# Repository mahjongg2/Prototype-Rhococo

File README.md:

# Prototype-Rhococo
Prototype of my Retro Home color computer, a 8-bit Z80 based home computer remake with 128 (bank switched) RAM, that uses a Parallax propeller chip for all the stuff that homecomputers from the previous century did with lots of simple CMOS logic circuits and sometimes dedicated VLSI chips did, such as generating TV pictures, and sound.
My rhococo should be able to generate 27 colors of VGA video in 512 x 480 resolution, and should be able to generate PSG quality sound. 
instead of relying on cassette tapes, of floppy-disks, it can use SD-cards. It doesn't store its permanent memory on (E)PROMS but on a serial EEPROM read out by the propeller,and copied to Z80 RAM at boot time. 
Its not based on any one retro computer but borrows ideas from all of them, mainly from the sinclair spectrum, Commodore 64, and MSX computers.

on these page I will commit CAD files, (main page is Rhococo.sch with sub-schematics Z80CPU+RAM.sch, and KEYBOARD.sch, and RHOCOCO.kicad.PCB for the layout) , but eventually I will also upload ideas, code and other stuff so that others can also build and test prototypes of my retro home computer.

Note that I explicitly call this a prototype, as Rhococo is still in development, and not a fully functioning device.
Lots of things are not even tested yet, as for testing them other stuff must work first.

If hardware bugs are found I will upload updated files fo new PCBś, and/or information to patch existing PCB's.

Weekly updated information and progress reports will be posted on my Wiki at: https://revspace.nl/Designing_the_RhoCoCo_Retro_Home_COlor_COmputer_hardware

if you want to discuss this meaterial with me, the best place for now would be here: https://www.raspberrypi.org/forums/viewtopic.php?f=62&t=226889

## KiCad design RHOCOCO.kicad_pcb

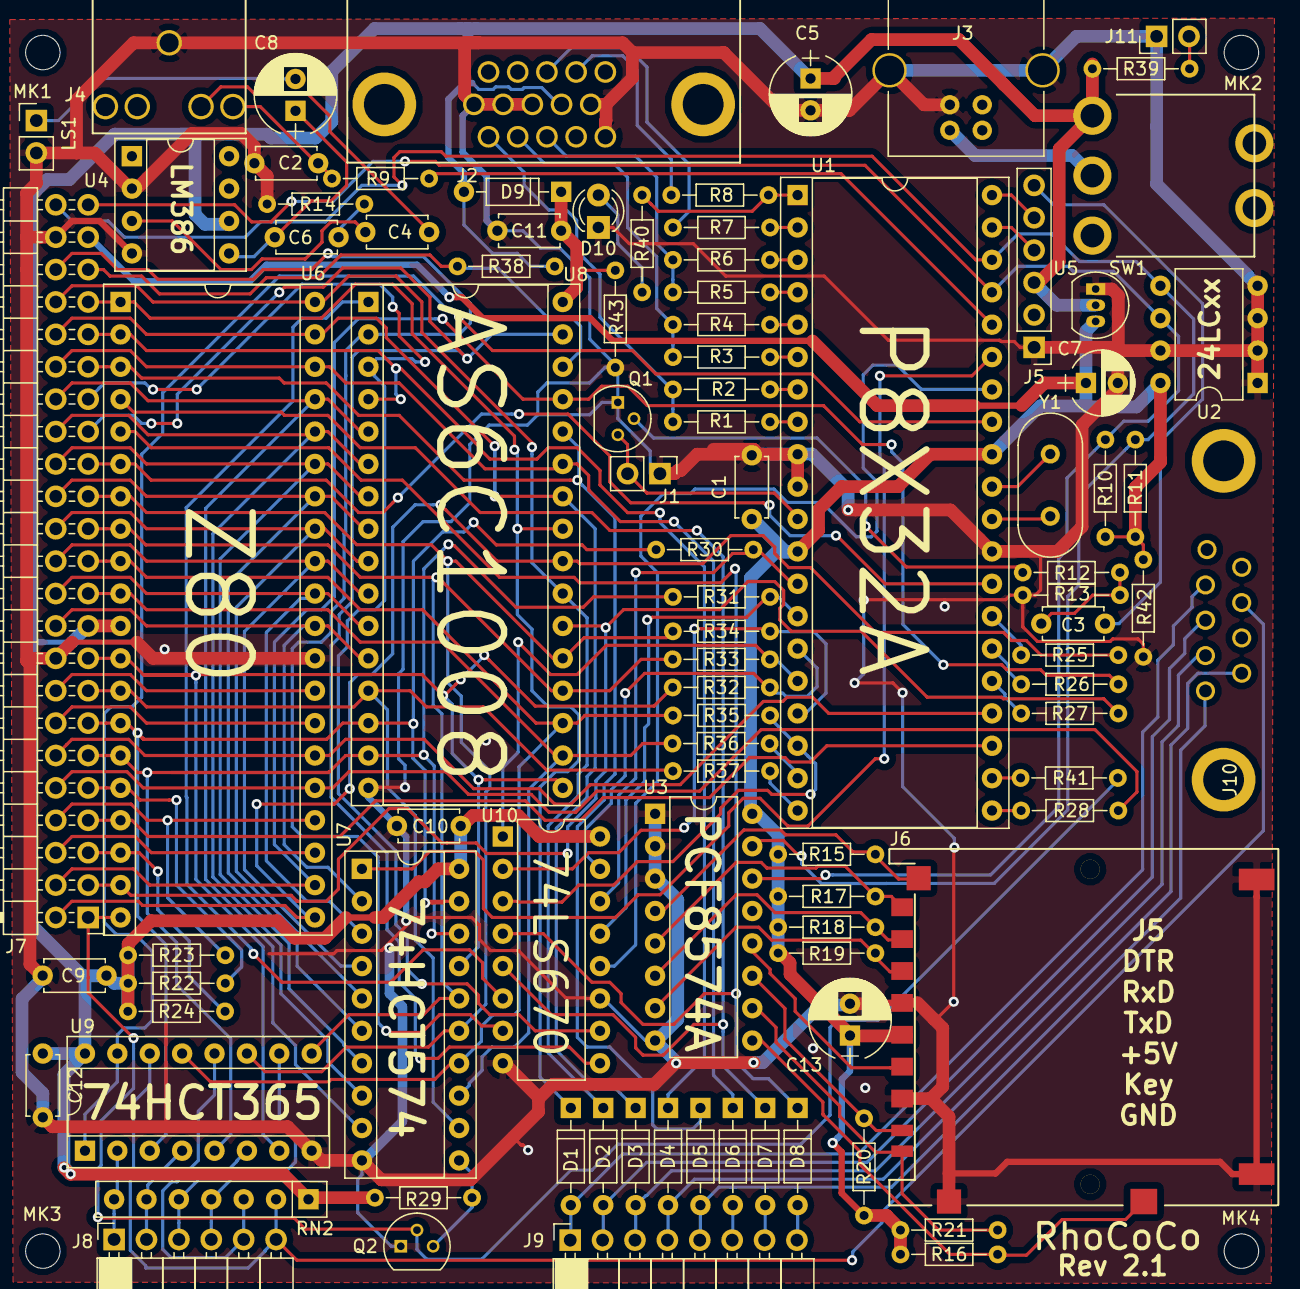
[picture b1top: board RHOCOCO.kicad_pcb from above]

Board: 2 copper layers, 97 parts (0 on the bottom side), 119 nets.

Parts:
C1, C3, C4, C9, C10, C11, C12: 100nF; C_Disc_D4.7mm_W2.5mm_P5.00mm
C2: 10nF; C_Disc_D4.7mm_W2.5mm_P5.00mm
C5: 100uF 16V; CP_Radial_D6.3mm_P2.50mm
C6: 4.7nF; C_Disc_D4.7mm_W2.5mm_P5.00mm
C7: 10uF 16V; CP_Radial_D5.0mm_P2.50mm
C8, C13: 220uF 10V; CP_Radial_D6.3mm_P2.50mm
D1, D2, D3, D4, D5, D6, D7, D8, D9: 1N4148; D_DO-35_SOD27_P7.62mm_Horizontal
D10: LED; LED_D3.0mm
J1, J11: CONN_01X02; Pin_Header_Straight_1x02_Pitch2.54mm
J2: VGA; VGA_connector
J3: USB_B
J4: Audio-Jack-3_2Switches; SPC21348
J5: CONN_01X06; Pin_Header_Straight_1x06_Pitch2.54mm
J6: SD_Card; SD-67600-006
J7: CONN_02X23; Pin_Header_Angled_2x23_Pitch2.54mm
J8: CONN_01X06; Socket_Strip_Angled_1x06_Pitch2.54mm
J9: CONN_01X08; Socket_Strip_Angled_1x08_Pitch2.54mm
J10: DB9_MALE; dB09-MALE
LS1: Speaker; Pin_Header_Straight_1x02_Pitch2.54mm
MK1, MK2, MK3, MK4: Mounting_Hole; MountingHole_2.7mm_M2.5
Q1: 2N3904; TO-92_Molded_Narrow
Q2: 2N7000; TO-92_Molded_Narrow
R1, R3, R5, R7, R8: 240R; R_Axial_DIN0204_L3.6mm_D1.6mm_P7.62mm_Horizontal
R2, R4, R6: 470R; R_Axial_DIN0204_L3.6mm_D1.6mm_P7.62mm_Horizontal
R9, R13, R15, R16, R22, R23, R24, R25, R26, R27, R28, R29, R38, R41: 10K; R_Axial_DIN0204_L3.6mm_D1.6mm_P7.62mm_Horizontal
R10, R11, R43: 4K7; R_Axial_DIN0204_L3.6mm_D1.6mm_P7.62mm_Horizontal
R12: 270; R_Axial_DIN0204_L3.6mm_D1.6mm_P7.62mm_Horizontal
R14: 10; R_Axial_DIN0204_L3.6mm_D1.6mm_P7.62mm_Horizontal
R17, R18, R19, R20, R21: 100K; R_Axial_DIN0204_L3.6mm_D1.6mm_P7.62mm_Horizontal
R30, R31, R32, R33, R34, R35, R36, R37, R40: 1K; R_Axial_DIN0204_L3.6mm_D1.6mm_P7.62mm_Horizontal
R39: 270R; R_Axial_DIN0204_L3.6mm_D1.6mm_P7.62mm_Horizontal
R42: 3K3; R_Axial_DIN0204_L3.6mm_D1.6mm_P7.62mm_Horizontal
RN2: 4K7 x 6 SIP; R_Array_SIP7
SW1: SW_SPDT; SWITCH-300SP1J1BLKM6QE
U1: P8X32A; DIP-40_W15.24mm_Socket
U2: 24LC256; DIP-8_W7.62mm
U3: PCF8574A; DIP-16_W7.62mm
U4: LM386; DIP-8_W7.62mm_Socket
U5: MCP1700-3302E_TO92; TO-92_Inline_Narrow_Oval
U6: Z80CPU; DIP-40_W15.24mm_Socket
U7: 74HCT574; DIP-20_W7.62mm_Socket
U8: AS6C1008; DIP-32_W15.24mm_Socket
U9: 74HCT365; DIP-16_W7.62mm_Socket
U10: 74HCT670; DIP-16_W7.62mm
Y1: 5MHz; Crystal_HC49-U_Vertical

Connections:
+3V3: C1.1, C7.1, C13.1, J6.4, J7.43, R10.2, R11.2, R15.2, R16.2, R17.2, R18.2, R19.2, R20.2, R21.2, R42.2, U1.12, U1.32, U2.8, U3.16, U5.3
+5V: C5.1, C9.2, C10.1, C12.1, D9.2, J2.9, J5.3, J7.19, R22.2, R23.2, R24.2, R29.1, R38.2, R39.2, RN2.1, SW1.1, U4.6, U5.2, U6.11, U7.20, U9.16, U10.16
/BLUE: J2.3, R5.2, R6.2
/DTR: C3.1, J5.6
/GREEN: J2.2, R3.2, R4.2
/H-SYN: J2.13, R7.2
/PWM_AUDIO: R9.1, U1.36
/RED: J2.1, R1.2, R2.2
/RXD: J5.5, U1.40
/TXD: J5.4, U1.39
/V-SYN: J2.14, R8.2
/z80ram/IORQ: Q2.3, R29.2, U7.11
/z80ram/KEYBOARD/KeyAddress8: D6.2, J9.6
/z80ram/KEYBOARD/KeyAddress9: D3.2, J9.3, J10.2
/z80ram/KEYBOARD/KeyAddress10: D2.2, J9.2, J10.3
/z80ram/KEYBOARD/KeyAddress11: D1.2, J9.1, J10.4
/z80ram/KEYBOARD/KeyAddress12: D4.2, J9.4, J10.6
/z80ram/KEYBOARD/KeyAddress13: D5.2, J9.5, J10.1
/z80ram/KEYBOARD/KeyAddress14: D7.2, J9.7
/z80ram/KEYBOARD/KeyAddress15: D8.2, J9.8
/z80ram/KEYBOARD/KeyData0: J8.1, RN2.7, U9.2
/z80ram/KEYBOARD/KeyData1: J8.2, RN2.6, U9.4
/z80ram/KEYBOARD/KeyData2: J8.3, RN2.5, U9.6
/z80ram/KEYBOARD/KeyData3: J8.4, RN2.4, U9.10
/z80ram/KEYBOARD/KeyData4: J8.5, RN2.3, U9.12
/z80ram/KEYBOARD/KeyData5: J8.6, J10.8, RN2.2, U9.14
/z80ram/RAM-A14: J7.33, U8.3, U10.10
/z80ram/RAM-A15: J7.31, U8.31, U10.9
/z80ram/RAM-A16: J7.42, U8.2, U10.7
/z80ram/RAM-A17: U8.1, U10.6
/z80ram/Z80-A0: J7.20, U6.30, U7.2, U8.12
/z80ram/Z80-A1: J7.22, U6.31, U7.3, U8.11
/z80ram/Z80-A2: J7.24, U6.32, U7.4, U8.10
/z80ram/Z80-A3: J7.26, U6.33, U7.5, U8.9
/z80ram/Z80-A4: J7.28, U6.34, U7.6, U8.8
/z80ram/Z80-A5: J7.30, U6.35, U7.7, U8.7
/z80ram/Z80-A6: J7.32, U6.36, U7.8, U8.6
/z80ram/Z80-A7: J7.34, U6.37, U7.9, U8.5
/z80ram/Z80-D6: J7.21, R36.1, U6.10, U7.13, U8.18
/z80ram/Z80-D7: J7.15, R37.1, U6.13, U7.12, U8.13
/z80ram/nBUSACK: J7.6, U6.23
/z80ram/nBUSREQ: J7.10, R28.1, U6.25
/z80ram/nDisable-RAM/A18: J7.41, R38.1, U8.30
/z80ram/nHALT: J7.5, R24.1, U6.18
/z80ram/nINT: J7.9, R22.1, U6.16
/z80ram/nIOREQ: J7.1, Q2.2, R41.1, U6.20
/z80ram/nM1: J7.14, U6.27
/z80ram/nMREQ: J7.3, R27.1, U6.19, U8.22
/z80ram/nRD: J7.2, R25.1, U6.21, U8.24
/z80ram/nRFSH: J7.16, U6.28
/z80ram/nWAIT: J7.8, R23.1, U6.24
/z80ram/nWR: J7.4, R26.1, U6.22, U8.29
GND: C1.2, C2.2, C5.2, C7.2, C9.1, C10.2, C11.2, C12.2, C13.2, D10.1, J1.1, J2.5, J2.6, J2.7, J2.8, J2.10, J3.4, J3.5, J4.3, J5.1, J6.3, J6.6, J6.12, J6.13, J7.18, J7.44, J11.1, LS1.2, Q1.1, Q2.1, R13.2, R14.1, R42.1, R43.2, U1.9, U1.10, U1.29, U2.1, U2.2, U2.3, U2.4, U2.7, U3.1, U3.2, U3.3, U3.8, U4.2, U4.4, U5.1, U6.29, U7.10, U8.16, U9.8, U10.8, U10.11
I2C-SCL: J7.45, R10.1, U1.37, U2.6, U3.14
I2C-SDA: J7.46, R11.1, U1.38, U2.5, U3.15
unnamed: C2.1, J4.1, R9.2
unnamed: C3.2, R12.1, R13.1
unnamed: C4.1, U4.3
unnamed: C4.2, J4.4
unnamed: C6.1, C8.1, U4.5
unnamed: C6.2, R14.2
unnamed: C8.2, LS1.1
unnamed: C11.1, D9.1, R43.1, U8.32
unnamed: D10.2, R40.2
unnamed: J1.2, Q1.3, U1.11
unnamed: J3.1, SW1.2
unnamed: J6.1, R18.1, U3.6
unnamed: J6.2, R19.1, U3.7
unnamed: J6.5, U3.12
unnamed: J6.7, R20.1, U3.11
unnamed: J6.8, R21.1, U3.10
unnamed: J6.9, R17.1, U3.5
unnamed: J6.10, R15.1, U3.4
unnamed: J6.11, R16.1, U3.9
unnamed: J11.2, R39.1
unnamed: Q1.2, R12.2
unnamed: R1.1, U1.8
unnamed: R2.1, U1.7
unnamed: R3.1, U1.6
unnamed: R4.1, U1.5
unnamed: R5.1, U1.4
unnamed: R6.1, U1.3
unnamed: R7.1, U1.2
unnamed: R8.1, R40.1, U1.1
unnamed: U1.30, Y1.2
unnamed: U1.31, Y1.1
PROP-D0: R30.2, U1.13, U10.14
PROP-D1: R31.2, U1.14, U10.13
PROP-D2: R32.2, U1.15, U10.15
PROP-D3: R33.2, U1.16, U10.1
PROP-D4: R34.2, U1.17, U10.2
PROP-D5: R35.2, U1.18, U10.3
PROP-D6: R36.2, U1.19
PROP-D7: R37.2, U1.20
PROP-nBUSRQ: R28.2, U1.21
PROP-nMREQ: R27.2, U1.25
PROP-nRD: R25.2, U1.27
PROP-nRDADR: U1.35, U7.1
PROP-nWR: R26.2, U1.26
Z80-A8: D6.1, J7.36, U6.38, U8.27
Z80-A9: D3.1, J7.38, U6.39, U8.26
Z80-A10: D2.1, J7.40, U6.40, U8.23
Z80-A11: D1.1, J7.39, U6.1, U8.25
Z80-A12: D4.1, J7.37, U6.2, U8.4
Z80-A13: D5.1, J7.35, U6.3, U8.28
Z80-A14: D7.1, U6.4, U10.5
Z80-A15: D8.1, U6.5, U10.4
Z80-D0: J7.13, R30.1, U6.14, U7.19, U8.14, U9.3
Z80-D1: J7.11, R31.1, U6.15, U7.18, U8.15, U9.5
Z80-D2: J7.17, R32.1, U6.12, U7.17, U8.17, U9.7
Z80-D3: J7.25, R33.1, U6.8, U7.16, U8.20, U9.9
Z80-D4: J7.27, R34.1, U6.7, U7.15, U8.21, U9.11
Z80-D5: J7.23, R35.1, U6.9, U7.14, U8.19, U9.13
Z80-nCLK: J7.29, U1.28, U6.6
Z80-nIORQ: R41.2, U1.22
Z80-nNMI: J7.7, U1.23, U6.17
Z80-nRESET: J7.12, U1.24, U6.26
nKEYBOARD_READ: U1.33, U9.1, U9.15
nWR_4X4: U1.34, U10.12

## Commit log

2019-09-11 Add files via upload
    The latest schematics (revision 4.0 September 2019)
2019-09-11 Add files via upload
    Gerber and drill files to produce Rhococo prototype PCB's updated to september 2019 (rev 2.1)
2019-09-11 Add files via upload
    KiCad schematic files
2019-09-11 Add files via upload
    Rhococo rev 2.1 layout file
